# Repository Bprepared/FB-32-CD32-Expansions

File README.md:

# FB-32-CD32-Expansions

This is a Commodore Amiga CD32 Expansion Project. The core of which is the FB-32R Riser which has been verified as working with the TerribleFire TF328

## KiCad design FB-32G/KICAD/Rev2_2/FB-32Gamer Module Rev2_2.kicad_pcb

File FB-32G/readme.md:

# FB-32G CD32 Riser Gamer Module

This is first module created for the FB-32R CD32 Riser
It has the following features:

Amiga 23pin Scart Video Connector (non-Genlock)

Minimig Scart output (with Ian Stedmans 3.3V Sync level correction which is selectable via jumper JP1)

Audio Jack

PS/2 Keyboard Interface - using the PIC16F628A (in a SSOP Package) running the same code as Kipper2K's CD32 riser

RS232 Serial - Basic Non-handshaking

# Build Notes:
Solder the PIC Microcontroller first and program it before adding any other componenets due to pin 4 being being used as part of the keyboard implementation and causes issues with programming once the board is built...you have been warned!

## License

This project and all the files contained are released under the GNU GPLv2. If you build a modified version of the board you must supply the end user with all the sources (this can be a web link).

# Bill of Materials

|Part | Value | Device | Package | Description |
|-----|-------|--------|---------|-------------|
| IC1  |       |SN74LVC1G97| SOT-23-6 | Configurable Gate |
| IC2  |       |SN74LVC1G97| SOT-23-6 | Configurable Gate |
| IC3  |       |SRV05-4| SOT-23-6 | Diode Array           |
| IC4  |       |PIC16F628A|SSOP-20| Microcontroller       |
| IC5  |       |MAX3311|uMAX-10| RS-232 Tranceiver        |
| U1   |       |LM1117-3.3| SOT-223 | Voltage Regulator   |
| C1   | 10uF  |Capacitor| 1206 | Ceramic                 |
| C2   | 10uF  |Capacitor| 1206 | Ceramic                 |
| C3   | 100nF |Capacitor| 0603 | Ceramic                 |
| C4   | 100nF |Capacitor| 3x5.3mm | Electrolytic         |
| C5   | 100nF |Capacitor| 3x5.3mm | Electrolytic         |
| C6   | 100nF |Capacitor| 0603 | Ceramic                 |
| C7   | 6800pF|Capacitor| 0603 | Ceramic                 |
| C8   | 6800pF|Capacitor| 0603 | Ceramic                 |
| C9   | 100nF |Capacitor| 0603 | Ceramic                 |
| C10  | 100nF |Capacitor| 0603 | Ceramic                 |
| D7   |       |1N914| SOD-323 | Diode                    |
| R1   | 75R   |Resistor| 0603 |                          |
| R2   | 75R   |Resistor| 0603 |                          |
| R3   | 1K    |Resistor| 0603 |                          |
| R4   | 75R   |Resistor| 0603 |                          |
| R5   | 75R   |Resistor| 0603 |                          |
| R6   | 75R   |Resistor| 0603 |                          |
| R7   | 75R   |Resistor| 0603 |                          |
| R8   | 10K   |Resistor| 0603 |                          |
| J1   |       |Connector| DB23M | D-Sub Male             |
| J2   |       |Connector| DB15F | D-Sub Female Hi Density|
| J3   |       |Connector| MD-60SV | 6 Pin Mini DIN       |
| J4   |       |Connector| DB9F  | D-Sub Female           |
| J5   |       |Connector| CP-3523SJR-ND | SMD 3.5mm Jack |
| J6   |       |Header| 2.54mm Male 1x06  | PIC ICSP      |
| J7   |       |Header| 2mm Male 2x05 | Video Breakout    |
| JP1  |       |Header| 2.54mm Male 1x03 | Sync Select    |

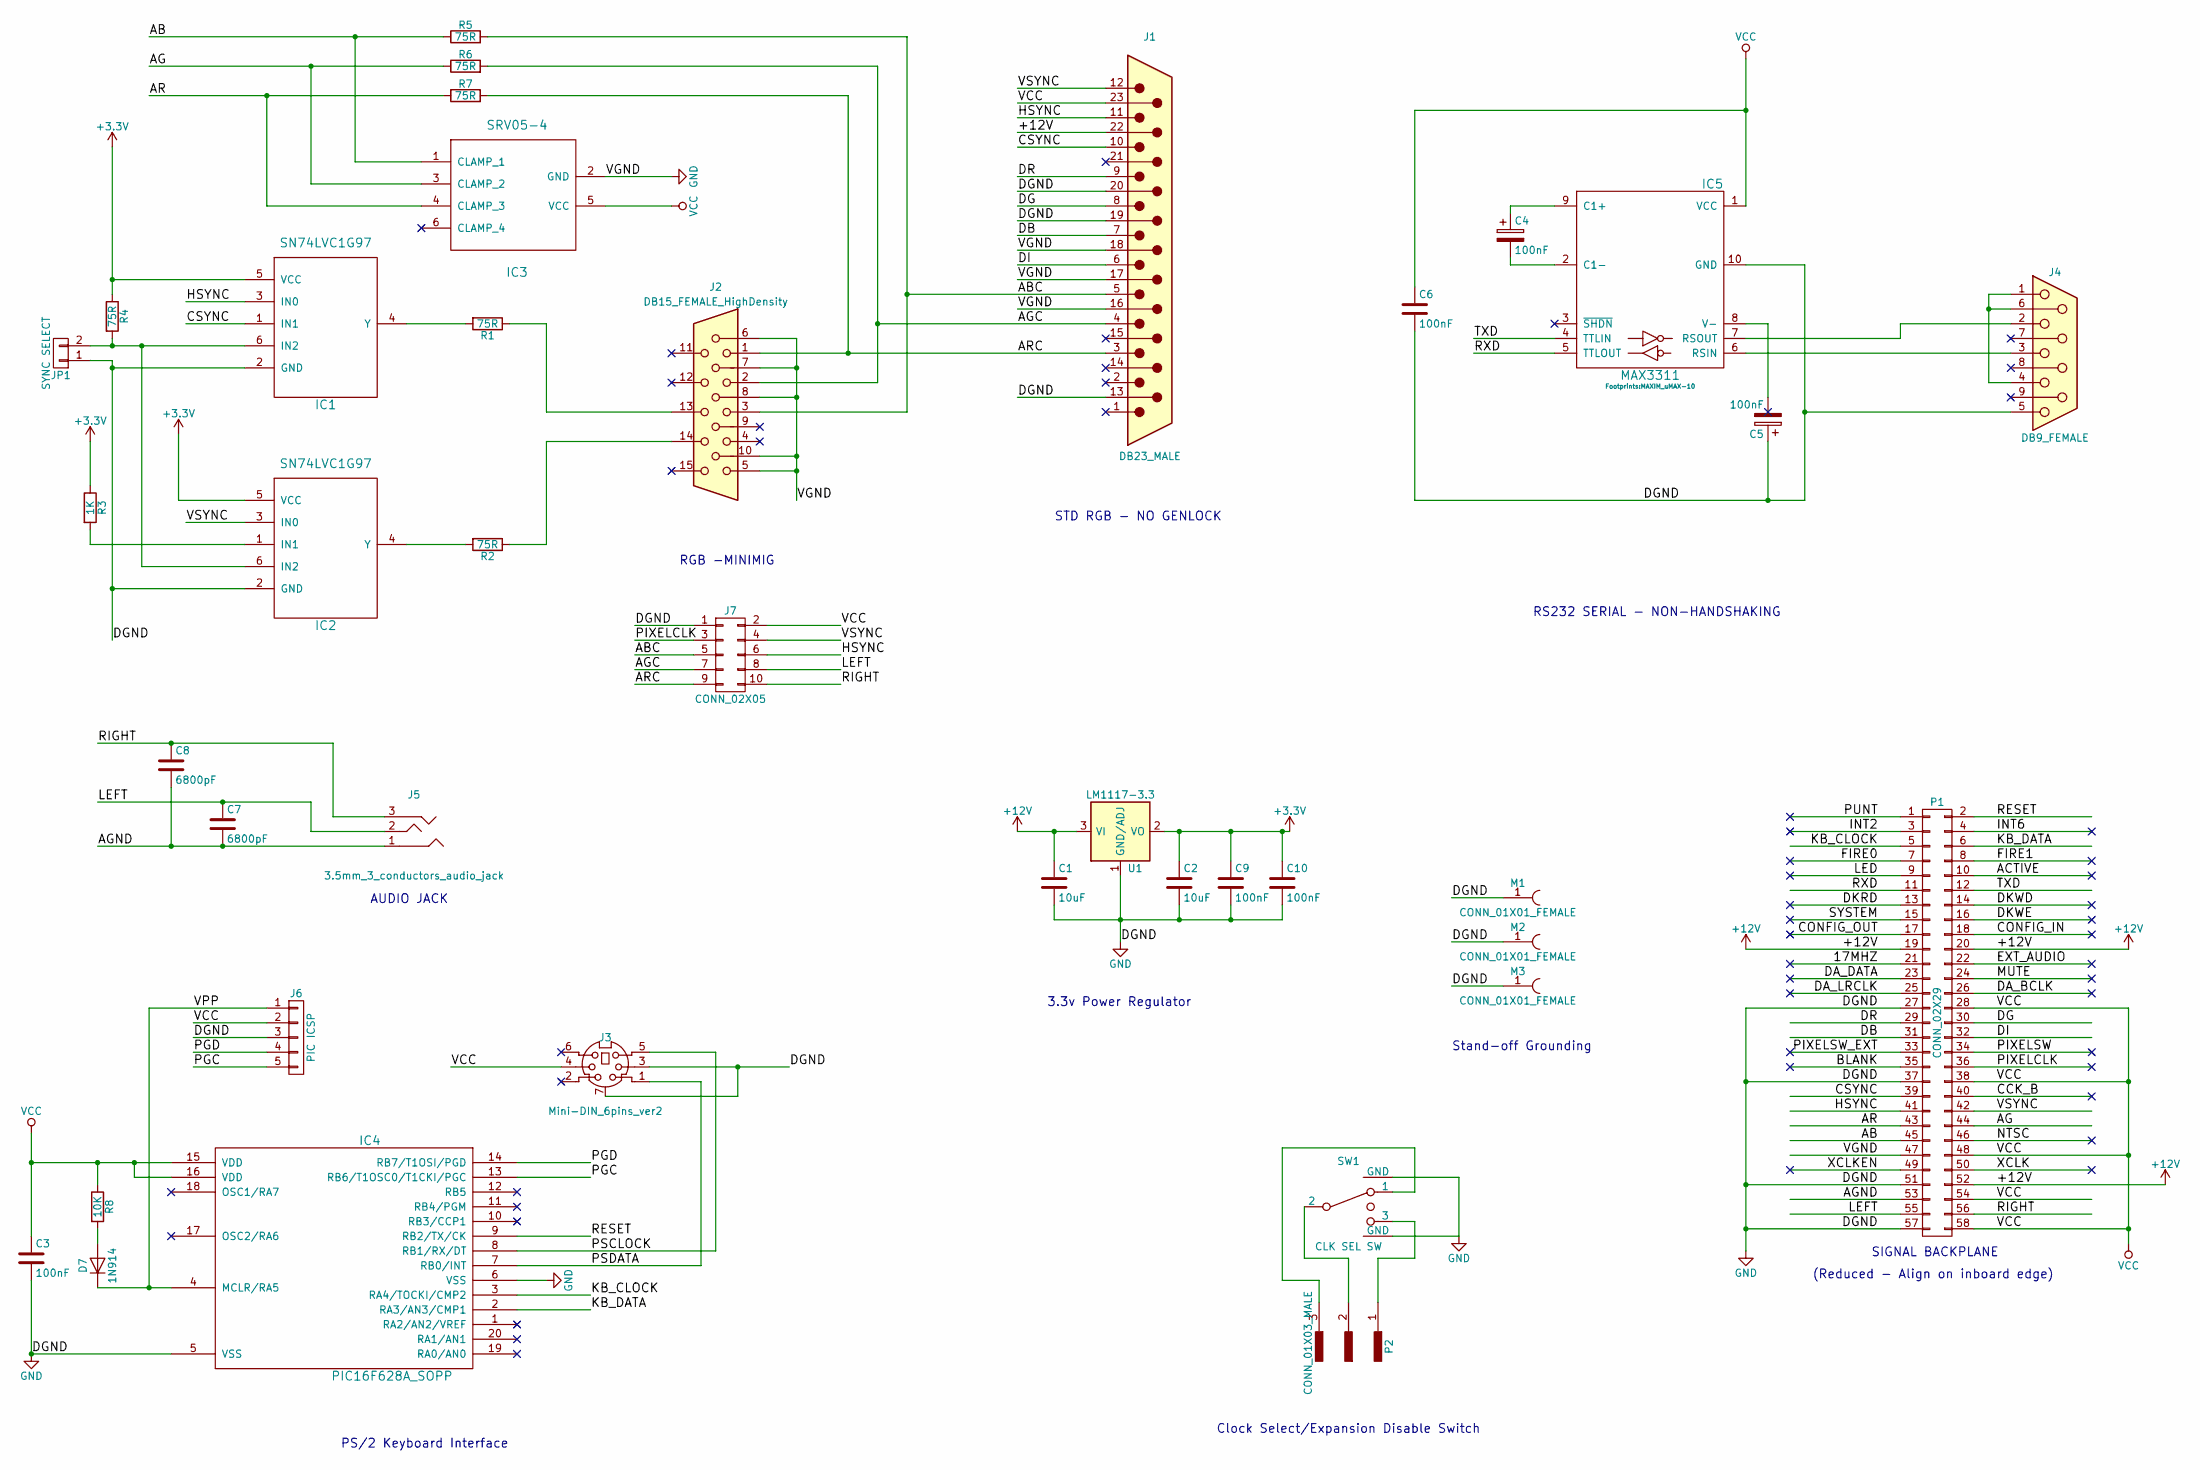
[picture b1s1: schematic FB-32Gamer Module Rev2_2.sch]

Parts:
C1, C2: 10uF; C_1206_HandSoldering
C3, C6, C9, C10: 100nF; C_0603_HandSoldering
C4, C5: 100nF; CP_Elec_3x5.3
C7, C8: 6800pF; C_0603_HandSoldering
D7: 1N914; D_SOD-323_HandSoldering
IC1, IC2: SN74LVC1G97; SOT-23-6_Handsoldering
IC3: SRV05-4; SOT-23-6_Handsoldering
IC4: PIC16F628A_SOPP; SSOP-20_5.3x7.2mm_Pitch0.65mm
IC5: MAX3311; MAXIM_uMAX-10
J1: DB23_MALE; DB23MDSB
J2: DB15_FEMALE_HighDensity; DB15HD_F
J3: Mini-DIN_6pins_ver2; MD-60SV_6Pin_MiniDIN
J4: DB9_FEMALE; DB9FD
J5: 3.5mm_3_conductors_audio_jack; CP-3523SJTR-ND_SMT_AUDIO_JACK
J6: PIC ICSP; Pin_Header_Straight_1x05_Pitch2.54mm
J7: CONN_02X05; Pin_Header_Angled_2x05_Pitch2.00mm
JP1: SYNC SELECT; Pin_Header_Straight_1x03_Pitch2.54mm
M1, M2, M3: CONN_01X01_FEMALE; 1pin
P1: CONN_02X29; Pin_Header_Straight_2x29_Pitch2.00mm
P2: CONN_01X03_MALE; Pin_Header_Angled_1x03_Pitch2.54mm
R1, R2, R4, R5, R6, R7: 75R; R_0603_HandSoldering
R3: 1K; R_0603_HandSoldering
R8: 10K; R_0603_HandSoldering
SW1: CLK SEL SW
U1: LM1117-3.3; SOT-223

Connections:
+3V3: C2.1, C9.1, C10.1, IC1.5 (VCC), IC2.5 (VCC), R3.1, R4.1, U1.2 (VO), U1.4 (VO)
+12V: C1.1, J1.22, P1.19, P1.20, P1.52, U1.3 (VI)
/17MHZ: P1.21
/AB: IC3.1 (CLAMP_1), P1.45, R5.1
/ABC: J1.5, J2.3, J7.5, R5.2
/ACTIVE: P1.10
/AG: IC3.3 (CLAMP_2), P1.44, R6.1
/AGC: J1.4, J2.2, J7.7, R6.2
/AGND: C7.2, C8.2, J5.1 (GND), P1.53
/AR: IC3.4 (CLAMP_3), P1.43, R7.1
/ARC: J1.3, J2.1, J7.9, R7.2
/BLANK: P1.35
/CCK_B: P1.40
/CONFIG_IN: P1.18
/CONFIG_OUT: P1.17
/CSYNC: IC1.1 (IN1), J1.10, P1.39
/DA_BCLK: P1.26
/DA_DATA: P1.23
/DA_LRCLK: P1.25
/DB: J1.7, P1.31
/DG: J1.8, P1.30
/DI: J1.6, P1.32
/DKRD: P1.13
/DKWD: P1.14
/DKWE: P1.16
/DR: J1.9, P1.29
/EXT_AUDIO: P1.22
/FIRE0: P1.7
/FIRE1: P1.8
/HSYNC: IC1.3 (IN0), J1.11, J7.6, P1.41
/INT2: P1.3
/INT6: P1.4
/KB_CLOCK: IC4.3 (RA4/TOCKI/CMP2), P1.5
/KB_DATA: IC4.2 (RA3/AN3/CMP1), P1.6
/LED: P1.9
/LEFT: C7.1, J5.2 (R), J7.8, P1.55
/MUTE: P1.24
/NTSC: P1.46
/PGC: IC4.13 (RB6/T1OSC0/T1CKI/PGC), J6.5
/PGD: IC4.14 (RB7/T1OSI/PGD), J6.4
/PIXELCLK: J7.3, P1.36
/PIXELSW: P1.34
/PIXELSW_EXT: P1.33
/PSCLOCK: IC4.8 (RB1/RX/DT), J3.5
/PSDATA: IC4.7 (RB0/INT), J3.1
/PUNT: P1.1
/RESET: IC4.9 (RB2/TX/CK), P1.2
/RIGHT: C8.1, J5.3 (L), J7.10, P1.56
/RXD: IC5.5 (TTLOUT), P1.11
/SYSTEM: P1.15
/TXD: IC5.4 (TTLIN), P1.12
/VPP: D7.1 (K), IC4.4 (MCLR/RA5), J6.1
/VSYNC: IC2.3 (IN0), J1.12, J7.4, P1.42
/XCLK: P1.50
/XCLKEN: P1.49
GND: C1.2, C2.2, C3.2, C5.1, C6.2, C9.2, C10.2, IC1.2 (GND), IC2.2 (GND), IC3.2 (GND), IC4.5 (VSS), IC4.6 (VSS), IC5.10 (GND), J1.13, J1.16, J1.17, J1.18, J1.19, J1.20, J2.5, J2.6, J2.7, J2.8, J2.10, J3.3, J3.7 (Shell), J4.5, J6.3, J7.1, JP1.1, M1.1, M2.1, M3.1, P1.27, P1.37, P1.47, P1.51, P1.57, SW1.4 (GND), SW1.5 (GND), U1.1 (GND/ADJ)
unnamed: C4.1, IC5.9 (C1+)
unnamed: C4.2, IC5.2 (C1-)
unnamed: C5.2, IC5.8 (V-)
unnamed: D7.2 (A), R8.2
unnamed: IC1.4 (Y), R1.2
unnamed: IC1.6 (IN2), IC2.6 (IN2), JP1.2, R4.2
unnamed: IC2.1 (IN1), R3.2
unnamed: IC2.4 (Y), R2.2
unnamed: IC5.6 (RSIN), J4.3
unnamed: IC5.7 (RSOUT), J4.2
unnamed: J2.13, R1.1
unnamed: J2.14, R2.1
unnamed: J4.1, J4.4, J4.6
unnamed: P2.1, SW1.3
unnamed: P2.2, SW1.2
unnamed: P2.3, SW1.1
VCC: C3.1, C6.1, IC3.5 (VCC), IC4.15 (VDD), IC4.16 (VDD), IC5.1 (VCC), J1.23, J3.4, J6.2, J7.2, P1.28, P1.38, P1.48, P1.54, P1.58, R8.1

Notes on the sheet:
SIGNAL BACKPLANE
RGB -MINIMIG
STD RGB - NO GENLOCK
RS232 SERIAL - NON-HANDSHAKING
3.3v Power Regulator
Clock Select/Expansion Disable Switch
PS/2 Keyboard Interface
Stand-off Grounding
(Reduced - Align on inboard edge)
AUDIO JACK

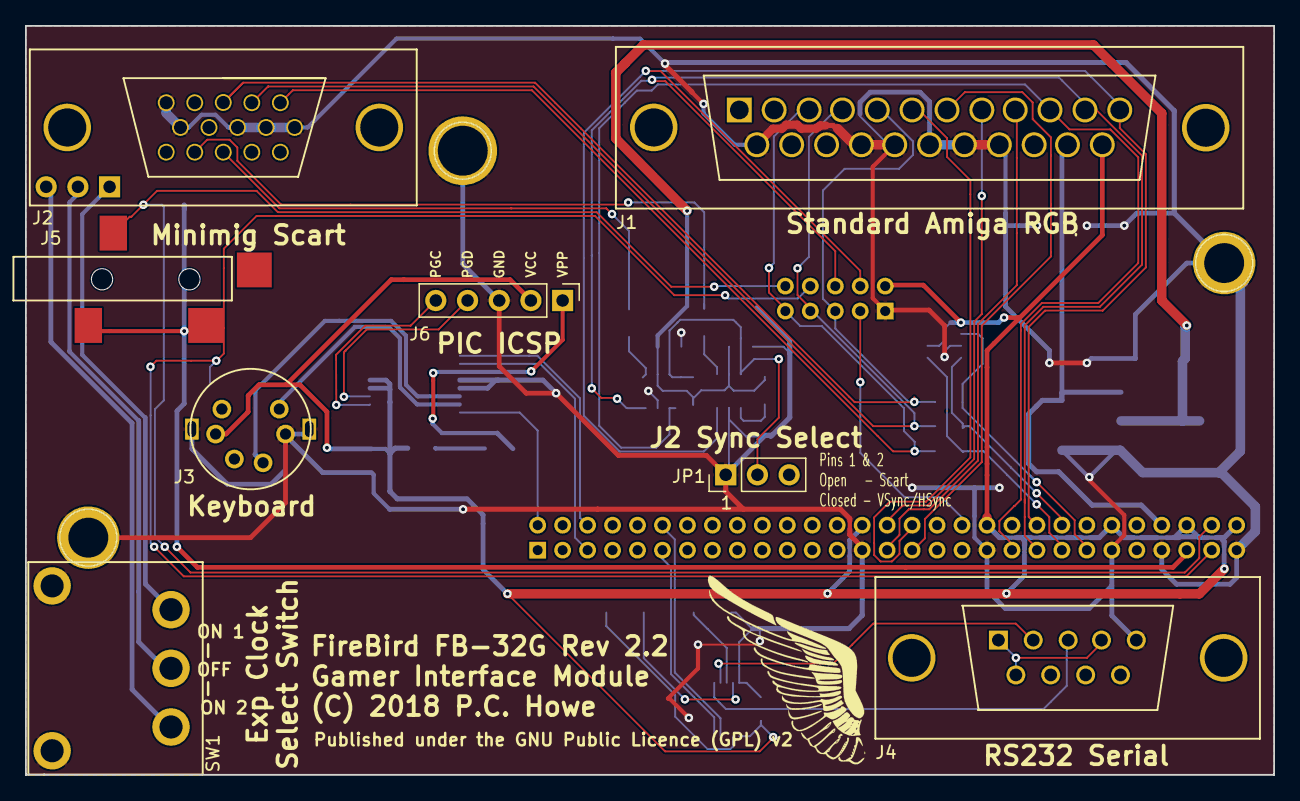
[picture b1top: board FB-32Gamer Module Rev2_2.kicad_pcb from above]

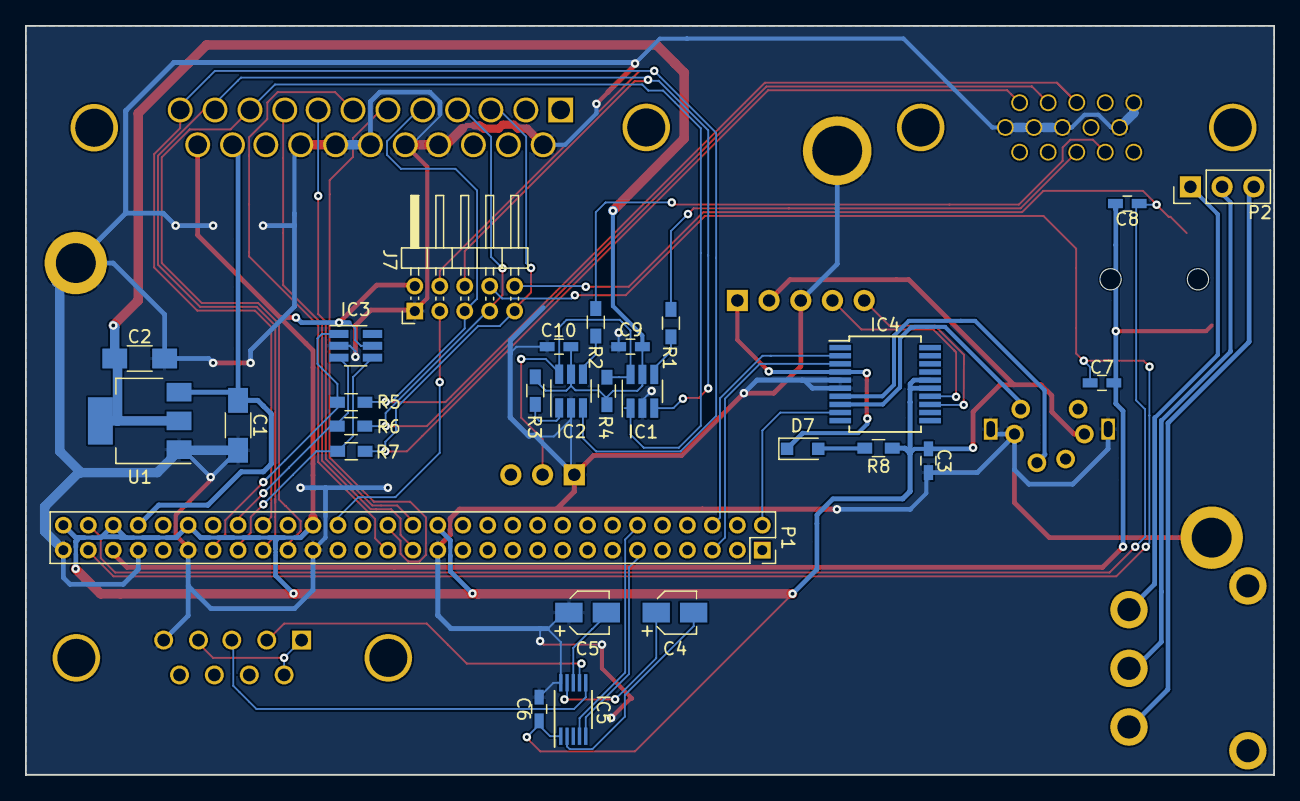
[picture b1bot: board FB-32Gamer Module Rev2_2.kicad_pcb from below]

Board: 2 copper layers, 100.0 x 60.0 mm, 39 parts (27 on the bottom side), 47 nets.

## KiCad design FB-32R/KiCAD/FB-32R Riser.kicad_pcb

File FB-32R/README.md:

# FB-32R CD32 Riser Board

Fundamentally, this is a passive board, with 2off 2x40 2mm Female Pin Headers giving 160 of the 182 signals from the CD32's edge connector. I choose to pull as many signals as I could, but drop those that were probably never going to be used i.e. the _EXT Video signals associated with the FMV module, and a few VCC/GNDS.
The female headers were selected as they allowed me to piggy back a second board on the back which will contain the magic, while not exposing pins to potential shorting. They can take 1A of current nicely, and the height of 2mm header male and female together are the same as standard PCB stand offs, so I don't have to rely on the connectors taking all the mechanical strain and abuse loads from plugging/unplugging cables, and I can develop different riser configurations with only needing to solder 160 through-hole pins (worst case) instead of 364!

## License

This project and all the files contained are released under the GNU GPLv2. If you build a modified version of the board you must supply the end user with all the sources (this can be a web link).

# Bill of Materials

|Part | Value | Device | Package | Description |
|-----|-------|--------|---------|-------------|
| J1  | CD32     |5650092-1| MCA-182 | Skt Edge Connector |
| J2  | EXP CARD |5650092-1| MCA-182 | Skt Edge Connector |
| J3  | BUSSES   |Header|2mm Female 2x40|                 |
| J4  | SIGNALS  |Header|2mm Female 2x40|                 |

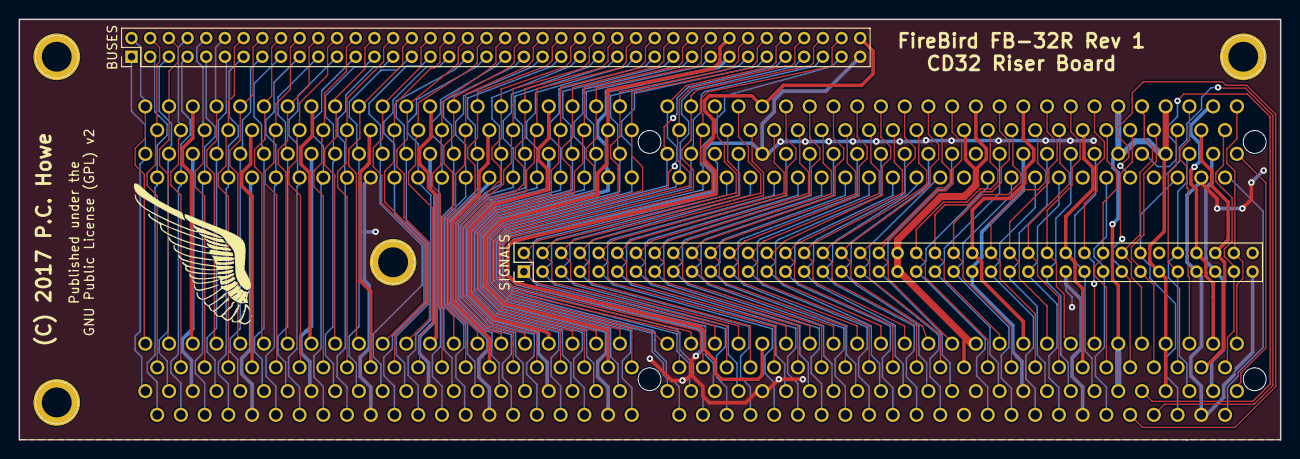
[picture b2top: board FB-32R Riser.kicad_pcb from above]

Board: 2 copper layers, 135.0 x 45.0 mm, 8 parts (0 on the bottom side), 153 nets.

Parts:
BUSES: CONN_02X40; Pin_Header_Straight_2x40_Pitch2.00mm
J1 - CD32, J2 - EXP CARD: MCA-182; MCA-182EDGESKT
M1, M2, M3, M4: CONN_01X01_FEMALE; 1pin
SIGNALS: CONN_02X40; Pin_Header_Straight_2x40_Pitch2.00mm

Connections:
/17MHZ: J1 - CD32.139, J2 - EXP CARD.139, SIGNALS.43
/+12V: J1 - CD32.136, J1 - CD32.138, J1 - CD32.178, J2 - EXP CARD.136, J2 - EXP CARD.138, J2 - EXP CARD.178, SIGNALS.41, SIGNALS.42, SIGNALS.74
/A0: BUSES.32, J1 - CD32.38, J2 - EXP CARD.38
/A1: BUSES.31, J1 - CD32.37, J2 - EXP CARD.37
/A2: BUSES.30, J1 - CD32.36, J2 - EXP CARD.36
/A3: BUSES.29, J1 - CD32.35, J2 - EXP CARD.35
/A4: BUSES.28, J1 - CD32.34, J2 - EXP CARD.34
/A5: BUSES.27, J1 - CD32.33, J2 - EXP CARD.33
/A6: BUSES.26, J1 - CD32.32, J2 - EXP CARD.32
/A7: BUSES.25, J1 - CD32.31, J2 - EXP CARD.31
/A8: BUSES.24, J1 - CD32.28, J2 - EXP CARD.28
/A9: BUSES.23, J1 - CD32.27, J2 - EXP CARD.27
/A10: BUSES.22, J1 - CD32.26, J2 - EXP CARD.26
/A11: BUSES.21, J1 - CD32.25, J2 - EXP CARD.25
/A12: BUSES.20, J1 - CD32.24, J2 - EXP CARD.24
/A13: BUSES.19, J1 - CD32.23, J2 - EXP CARD.23
/A14: BUSES.18, J1 - CD32.22, J2 - EXP CARD.22
/A15: BUSES.17, J1 - CD32.21, J2 - EXP CARD.21
/A16: BUSES.16, J1 - CD32.18, J2 - EXP CARD.18
/A17: BUSES.15, J1 - CD32.17, J2 - EXP CARD.17
/A18: BUSES.14, J1 - CD32.16, J2 - EXP CARD.16
/A19: BUSES.13, J1 - CD32.15, J2 - EXP CARD.15
/A20: BUSES.12, J1 - CD32.14, J2 - EXP CARD.14
/A21: BUSES.11, J1 - CD32.13, J2 - EXP CARD.13
/A22: BUSES.10, J1 - CD32.12, J2 - EXP CARD.12
/A23: BUSES.9, J1 - CD32.11, J2 - EXP CARD.11
/A24: BUSES.8, J1 - CD32.8, J2 - EXP CARD.8
/A25: BUSES.7, J1 - CD32.7, J2 - EXP CARD.7
/A26: BUSES.6, J1 - CD32.6, J2 - EXP CARD.6
/A27: BUSES.5, J1 - CD32.5, J2 - EXP CARD.5
/A28: BUSES.4, J1 - CD32.4, J2 - EXP CARD.4
/A29: BUSES.3, J1 - CD32.3, J2 - EXP CARD.3
/A30: BUSES.2, J1 - CD32.2, J2 - EXP CARD.2
/A31: BUSES.1, J1 - CD32.1, J2 - EXP CARD.1
/AB: J1 - CD32.168, J2 - EXP CARD.168, SIGNALS.67
/AB_EXT: J1 - CD32.167, J2 - EXP CARD.167
/ACTIVE: J1 - CD32.126, J2 - EXP CARD.126, SIGNALS.32
/AG: J1 - CD32.166, J2 - EXP CARD.166, SIGNALS.66
/AGND: J1 - CD32.177, J2 - EXP CARD.177, SIGNALS.75
/AG_EXT: J1 - CD32.165, J2 - EXP CARD.165
/AR: J1 - CD32.164, J2 - EXP CARD.164, SIGNALS.65
/AR_EXT: J1 - CD32.163, J2 - EXP CARD.163
/AS: BUSES.77, J1 - CD32.91, J2 - EXP CARD.91
/AVEC: J1 - CD32.96, J2 - EXP CARD.96, SIGNALS.4
/BERR: J1 - CD32.94, J2 - EXP CARD.94, SIGNALS.2
/BLANK: J1 - CD32.153, J2 - EXP CARD.153, SIGNALS.57
/CBACK: J1 - CD32.110, J2 - EXP CARD.110, SIGNALS.16
/CBREQ: J1 - CD32.109, J2 - EXP CARD.109, SIGNALS.15
/CCK_B: J1 - CD32.158, J2 - EXP CARD.158, SIGNALS.62
/CIIN: J1 - CD32.107, J2 - EXP CARD.107, SIGNALS.13
/CIOUT: J1 - CD32.108, J2 - EXP CARD.108, SIGNALS.14
/CONFIG_IN: J1 - CD32.134, J2 - EXP CARD.134, SIGNALS.40
/CONFIG_OUT: J1 - CD32.133, J2 - EXP CARD.133, SIGNALS.39
/CPUCLK_A: J1 - CD32.99, J2 - EXP CARD.99, SIGNALS.7
/CPU_BG: J1 - CD32.113, J2 - EXP CARD.113, SIGNALS.19
/CPU_BGACK: J1 - CD32.115, J2 - EXP CARD.115, SIGNALS.21
/CPU_BR: J1 - CD32.111, J2 - EXP CARD.111, SIGNALS.17
/CSYNC: J1 - CD32.157, J2 - EXP CARD.157, SIGNALS.61
/D0: BUSES.64, J1 - CD32.78, J2 - EXP CARD.78
/D1: BUSES.63, J1 - CD32.77, J2 - EXP CARD.77
/D2: BUSES.62, J1 - CD32.76, J2 - EXP CARD.76
/D3: BUSES.61, J1 - CD32.75, J2 - EXP CARD.75
/D4: BUSES.60, J1 - CD32.74, J2 - EXP CARD.74
/D5: BUSES.59, J1 - CD32.73, J2 - EXP CARD.73
/D6: BUSES.58, J1 - CD32.72, J2 - EXP CARD.72
/D7: BUSES.57, J1 - CD32.71, J2 - EXP CARD.71
/D8: BUSES.56, J1 - CD32.68, J2 - EXP CARD.68
/D9: BUSES.55, J1 - CD32.67, J2 - EXP CARD.67
/D10: BUSES.54, J1 - CD32.66, J2 - EXP CARD.66
/D11: BUSES.53, J1 - CD32.65, J2 - EXP CARD.65
/D12: BUSES.52, J1 - CD32.64, J2 - EXP CARD.64
/D13: BUSES.51, J1 - CD32.63, J2 - EXP CARD.63
/D14: BUSES.50, J1 - CD32.62, J2 - EXP CARD.62
/D15: BUSES.49, J1 - CD32.61, J2 - EXP CARD.61
/D16: BUSES.48, J1 - CD32.58, J2 - EXP CARD.58
/D17: BUSES.47, J1 - CD32.57, J2 - EXP CARD.57
/D18: BUSES.46, J1 - CD32.56, J2 - EXP CARD.56
/D19: BUSES.45, J1 - CD32.55, J2 - EXP CARD.55
/D20: BUSES.44, J1 - CD32.54, J2 - EXP CARD.54
/D21: BUSES.43, J1 - CD32.53, J2 - EXP CARD.53
/D22: BUSES.42, J1 - CD32.52, J2 - EXP CARD.52
/D23: BUSES.41, J1 - CD32.51, J2 - EXP CARD.51
/D24: BUSES.40, J1 - CD32.48, J2 - EXP CARD.48
/D25: BUSES.39, J1 - CD32.47, J2 - EXP CARD.47
/D26: BUSES.38, J1 - CD32.46, J2 - EXP CARD.46
/D27: BUSES.37, J1 - CD32.45, J2 - EXP CARD.45
/D28: BUSES.36, J1 - CD32.44, J2 - EXP CARD.44
/D29: BUSES.35, J1 - CD32.43, J2 - EXP CARD.43
/D30: BUSES.34, J1 - CD32.42, J2 - EXP CARD.42
/D31: BUSES.33, J1 - CD32.41, J2 - EXP CARD.41
/DA_BCLK: J1 - CD32.144, J2 - EXP CARD.144, SIGNALS.48
/DA_DATA: J1 - CD32.141, J2 - EXP CARD.141, SIGNALS.45
/DA_LRCLK: J1 - CD32.143, J2 - EXP CARD.143, SIGNALS.47
/DB: J1 - CD32.149, J2 - EXP CARD.149, SIGNALS.53
/DG: J1 - CD32.148, J2 - EXP CARD.148, SIGNALS.52
/DGND: BUSES.65, BUSES.79, J1 - CD32.9, J1 - CD32.19, J1 - CD32.29, J1 - CD32.39, J1 - CD32.49, J1 - CD32.59, J1 - CD32.69, J1 - CD32.79, J1 - CD32.101, J1 - CD32.135, J1 - CD32.137, J1 - CD32.145, J1 - CD32.155, J1 - CD32.175, J2 - EXP CARD.9, J2 - EXP CARD.19, J2 - EXP CARD.29, J2 - EXP CARD.39, J2 - EXP CARD.49, J2 - EXP CARD.59, J2 - EXP CARD.69, J2 - EXP CARD.79, J2 - EXP CARD.101, J2 - EXP CARD.135, J2 - EXP CARD.137, J2 - EXP CARD.145, J2 - EXP CARD.155, J2 - EXP CARD.175, M1.1, M2.1, M3.1, M4.1, SIGNALS.49, SIGNALS.59, SIGNALS.73, SIGNALS.79
/DI: J1 - CD32.150, J2 - EXP CARD.150, SIGNALS.54
/DKRD: J1 - CD32.129, J2 - EXP CARD.129, SIGNALS.35
/DKWD: J1 - CD32.130, J2 - EXP CARD.130, SIGNALS.36
/DKWE: J1 - CD32.132, J2 - EXP CARD.132, SIGNALS.38
/DR: J1 - CD32.147, J2 - EXP CARD.147, SIGNALS.51
/DS: BUSES.78, J1 - CD32.92, J2 - EXP CARD.92
/DSACK0: J1 - CD32.98, J2 - EXP CARD.98, SIGNALS.6
/DSACK1: J1 - CD32.97, J2 - EXP CARD.97, SIGNALS.5
/E: J1 - CD32.100, J2 - EXP CARD.100, SIGNALS.8
/ECS: BUSES.73, J1 - CD32.87, J2 - EXP CARD.87
/EXPBG: J1 - CD32.112, J2 - EXP CARD.112, SIGNALS.18
/EXP_BGACK: J1 - CD32.116, J2 - EXP CARD.116, SIGNALS.22
/EXP_BR: J1 - CD32.114, J2 - EXP CARD.114, SIGNALS.20
/EXT_AUDIO: J1 - CD32.140, J2 - EXP CARD.140, SIGNALS.44
/EXT_VIDEO: J1 - CD32.174, J2 - EXP CARD.174
/FC0: J1 - CD32.105, J2 - EXP CARD.105, SIGNALS.11
/FC1: J1 - CD32.104, J2 - EXP CARD.104, SIGNALS.10
/FC2: J1 - CD32.103, J2 - EXP CARD.103, SIGNALS.9
/FIRE0: J1 - CD32.123, J2 - EXP CARD.123, SIGNALS.29
/FIRE1: J1 - CD32.124, J2 - EXP CARD.124, SIGNALS.30
/HALT: BUSES.72, J1 - CD32.86, J2 - EXP CARD.86
/HSYNC: J1 - CD32.159, J2 - EXP CARD.159, SIGNALS.63
/INT2: J1 - CD32.119, J2 - EXP CARD.119, SIGNALS.25
/INT6: J1 - CD32.120, J2 - EXP CARD.120, SIGNALS.26
/IPEND: BUSES.70, J1 - CD32.84, J2 - EXP CARD.84
/IPL0: BUSES.69, J1 - CD32.83, J2 - EXP CARD.83
/IPL1: BUSES.68, J1 - CD32.82, J2 - EXP CARD.82
/IPL2: BUSES.67, J1 - CD32.81, J2 - EXP CARD.81
/KB_CLOCK: J1 - CD32.121, J2 - EXP CARD.121, SIGNALS.27
/KB_DATA: J1 - CD32.122, J2 - EXP CARD.122, SIGNALS.28
/LED: J1 - CD32.125, J2 - EXP CARD.125, SIGNALS.31
/LEFT: J1 - CD32.180, J2 - EXP CARD.180, SIGNALS.77
/LEFT_EXT: J1 - CD32.179, J2 - EXP CARD.179
/MUTE: J1 - CD32.142, J2 - EXP CARD.142, SIGNALS.46
/NTSC: J1 - CD32.171, J2 - EXP CARD.171, SIGNALS.68
/OCS: BUSES.74, J1 - CD32.88, J2 - EXP CARD.88
/PIXELCLK: J1 - CD32.154, J2 - EXP CARD.154, SIGNALS.58
/PIXELSW: J1 - CD32.152, J2 - EXP CARD.152, SIGNALS.56
/PIXELSW_EXT: J1 - CD32.151, J2 - EXP CARD.151, SIGNALS.55
/PUNT: J1 - CD32.117, J2 - EXP CARD.117, SIGNALS.23
/R/W: J1 - CD32.93, J2 - EXP CARD.93, SIGNALS.1
/RESET: J1 - CD32.118, J2 - EXP CARD.118, SIGNALS.24
/RIGHT: J1 - CD32.182, J2 - EXP CARD.182, SIGNALS.78
/RIGHT_EXT: J1 - CD32.181, J2 - EXP CARD.181
/RMC: J1 - CD32.106, J2 - EXP CARD.106, SIGNALS.12
/RST: BUSES.71, J1 - CD32.85, J2 - EXP CARD.85
/RXD: J1 - CD32.127, J2 - EXP CARD.127, SIGNALS.33
/SIZE0: BUSES.76, J1 - CD32.90, J2 - EXP CARD.90
/SIZE1: BUSES.75, J1 - CD32.89, J2 - EXP CARD.89
/STERM: J1 - CD32.95, J2 - EXP CARD.95, SIGNALS.3
/SYSTEM: J1 - CD32.131, J2 - EXP CARD.131, SIGNALS.37
/TXD: J1 - CD32.128, J2 - EXP CARD.128, SIGNALS.34
/VGND: J1 - CD32.161, J1 - CD32.162, J1 - CD32.169, J1 - CD32.170, J2 - EXP CARD.161, J2 - EXP CARD.162, J2 - EXP CARD.169, J2 - EXP CARD.170, SIGNALS.69
/VSYNC: J1 - CD32.160, J2 - EXP CARD.160, SIGNALS.64
/XCLK: J1 - CD32.173, J2 - EXP CARD.173, SIGNALS.72
/XCLKEN: J1 - CD32.172, J2 - EXP CARD.172, SIGNALS.71
VCC: BUSES.66, BUSES.80, J1 - CD32.10, J1 - CD32.20, J1 - CD32.30, J1 - CD32.40, J1 - CD32.50, J1 - CD32.60, J1 - CD32.70, J1 - CD32.80, J1 - CD32.102, J1 - CD32.146, J1 - CD32.156, J1 - CD32.176, J2 - EXP CARD.10, J2 - EXP CARD.20, J2 - EXP CARD.30, J2 - EXP CARD.40, J2 - EXP CARD.50, J2 - EXP CARD.60, J2 - EXP CARD.70, J2 - EXP CARD.80, J2 - EXP CARD.102, J2 - EXP CARD.146, J2 - EXP CARD.156, J2 - EXP CARD.176, SIGNALS.50, SIGNALS.60, SIGNALS.70, SIGNALS.76, SIGNALS.80

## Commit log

2017-10-27 Create LICENSE
2019-09-12 Create PH

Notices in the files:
FB-32G/KICAD/Rev2_2/FB-32Gamer Module Rev2_2.kicad_pcb:
(C) 2018 P.C. Howe
Published under the GNU Public Licence (GPL) v2
FB-32R/KiCAD/FB-32R Riser.kicad_pcb:
(C) 2017 P.C. Howe
GNU Public License (GPL) v2
